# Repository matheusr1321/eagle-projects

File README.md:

# eagle-projects
Para adicionar silkscreen, adiciona texto, mas seleciona a layer 21 - tplace
Para modificar footprint pra tirar texto indesejado deles ou mudar camada dos textos, clica com botão direito no componente, "open footprint"
Quando eu exportava as gerber file, os textos ficavam em negrito. é porque estavam em formato proporcional. para mudar, clica botão direito no texto, "properties", 
modifica proporcional para vector e muda o "ratio".

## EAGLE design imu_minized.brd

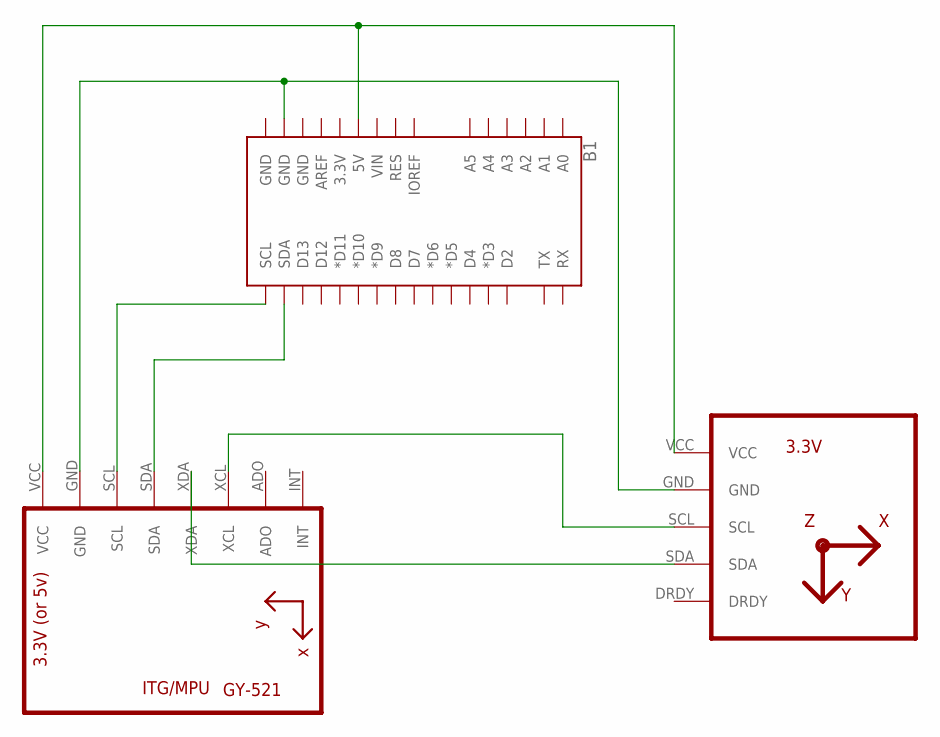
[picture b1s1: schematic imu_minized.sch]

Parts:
B1: ARDUINO_UNO_R3_SHIELDNOLABELS; UNO_R3_SHIELD_NOLABELS
U1: GY-521MPU6050; GY-521
U2: HMC5883LGY-271; GY-271

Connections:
unnamed: B1.5V, U1.VCC, U2.VCC
unnamed: B1.GND@1 (GND), U1.GND, U2.GND
unnamed: B1.SCL, U1.SCL
unnamed: B1.SDA, U1.SDA
unnamed: U1.XDA, U2.SDA
unnamed: U1.XCL, U2.SCL

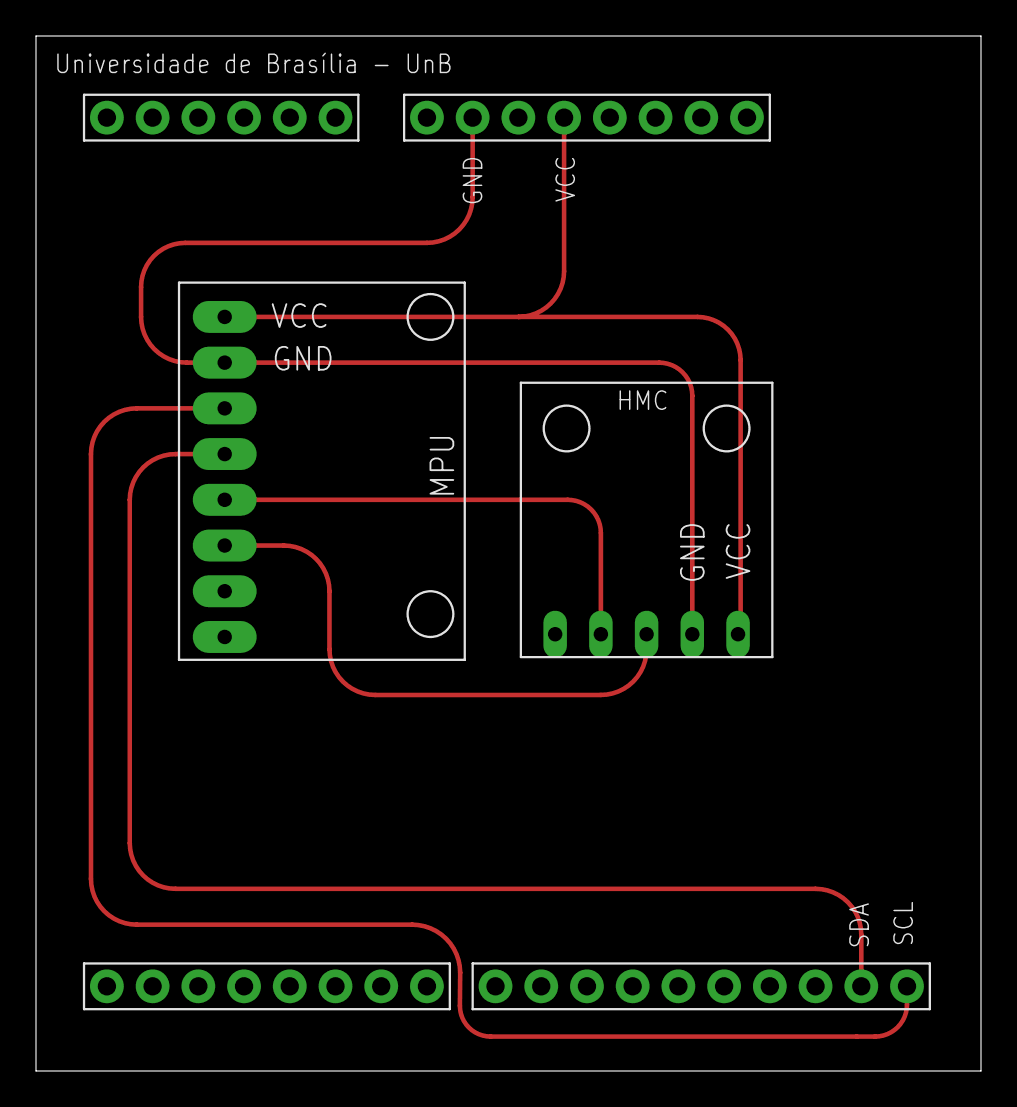
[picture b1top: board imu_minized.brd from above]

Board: 2 copper layers, 52.5 x 57.5 mm, 3 parts (1 on the bottom side), 6 nets.

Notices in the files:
parts and their libraries:
SparkFun-Boards: Licensing: Creative Commons ShareAlike 4.0 International - https://creativecommons.org/licenses/by-sa/4.0
